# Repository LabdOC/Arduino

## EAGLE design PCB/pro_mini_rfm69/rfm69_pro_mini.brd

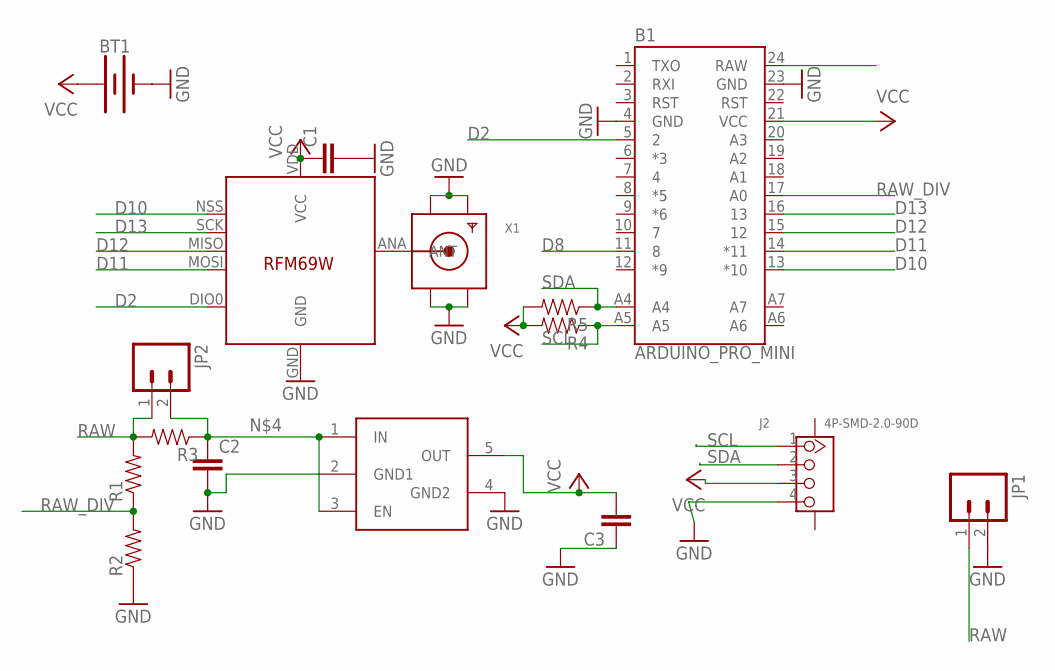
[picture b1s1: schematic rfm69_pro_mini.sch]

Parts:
B1: ARDUINO_PRO_MINI
BT1: BATTERY-20MM_PTH; BATTCOM_20MM_PTH
C1, C2, C3: CAP0805-CAP; 0805-CAP
J2: 4P-SMD-2.0-90D; HW4-SMD-2.0-90D
JP1, JP2: M02PTH; 1X02
R1, R2, R3, R4, R5: RESISTOR0805-RES; 0805-RES
U$1: TPS783; SOT23-5
U$2: RFM69; RFM69W-MINPADS
X1: SMACONNECTOR; SMA90_DIP

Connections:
D2: B1.5 (2), U$2.DIO0
D8: B1.11 (8)
D10: B1.13 (*10), U$2.NSS (SEL)
D11: B1.14 (*11), U$2.MOSI
D12: B1.15 (12), U$2.MISO
D13: B1.16 (13), U$2.SCK
GND: B1.4 (GND), B1.23 (GND), BT1.2 (-), C1.2, C2.2, C3.1, J2.4, JP1.2, R2.1, U$1.2 (GND1), U$1.4 (GND2), U$2.GND, X1.GND1, X1.GND2, X1.GND3, X1.GND4
unnamed: U$2.ANA (ANT), X1.ANTENNA (ANT)
unnamed: C2.1, JP2.2, R3.1, U$1.1 (IN), U$1.3 (EN)
RAW: JP1.1, JP2.1, R1.2, R3.2
RAW_DIV: B1.17 (A0), R1.1, R2.2
SCL: B1.A5, J2.1, R4.1
SDA: B1.A4, J2.2, R5.1
VCC: B1.21 (VCC), BT1.1 (+), C1.1, C3.2, J2.3, R4.2, R5.2, U$1.5 (OUT), U$2.VDD (VCC)

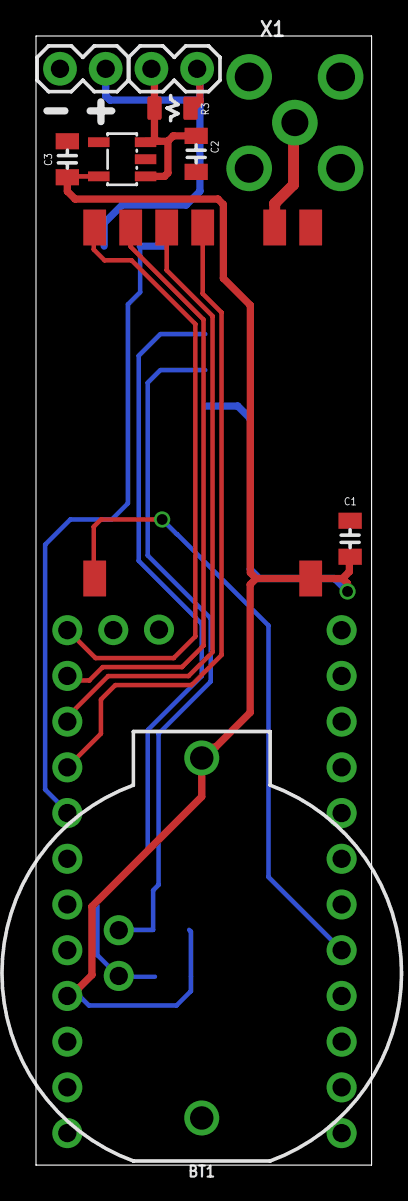
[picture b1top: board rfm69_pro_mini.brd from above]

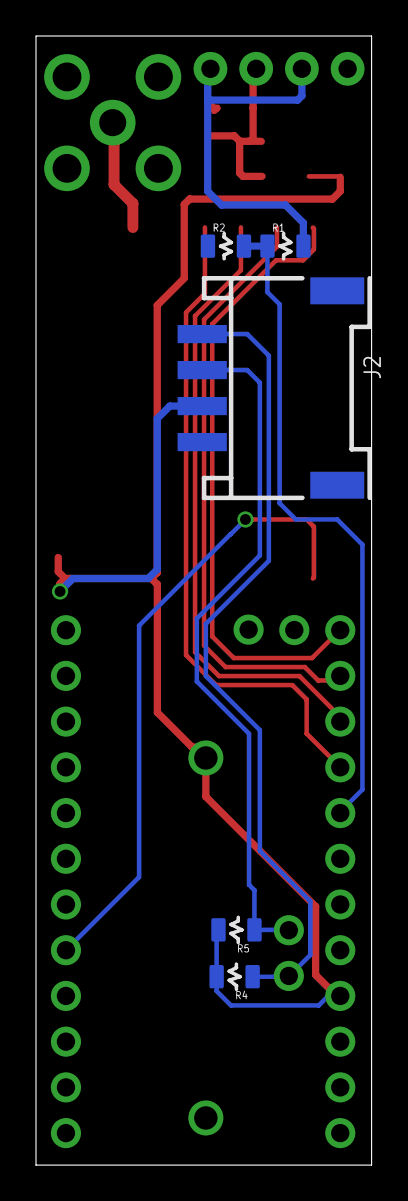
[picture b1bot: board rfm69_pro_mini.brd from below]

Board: 2 copper layers, 18.6 x 62.7 mm, 16 parts (5 on the bottom side), 13 nets.

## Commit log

2017-06-06 Added folder for PCB design files

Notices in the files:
parts and their libraries:
SparkFun-Boards: Licensing: Creative Commons ShareAlike 4.0 International - https://creativecommons.org/licenses/by-sa/4.0
